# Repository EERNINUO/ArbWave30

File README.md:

<div align="center">

<!-- Assisted-by: DeepSeek - 文档框架 -->

# ArbWave30
30MHz 任意波形发生器 | FPGA + 高速DAC | SCPI 可控 

<p align="center">

  <br/>

  <!--  -->
</p>
</div>

---

> **⚠️ 注意**：你当前查看的是 **develop** 开发分支，内容可能不稳定。
> 推荐使用稳定发布版本：[查看 Releases](https://github.com/EERNINUO/ArbWave30/tree/releases)

## ⚠️ 更新状态
作者正在参与《0854 不相信眼泪》（Author is currently involved in Chinese graduate entrance exam），本项目暂停更新，承诺 2026.12.25 恢复更新并发布第一个 Release。（你问我为什么不是 20 号就更新？好不容易解放了我不得爽玩几天）

## ✨ 特性

### 硬件指标（V1.0）
- 波形：正弦、方波、三角波、噪声波、直流
- 正弦波最高 **30MHz**，方波最高 **5MHz**
- 电压范围（高阻）：20Vpp（DC\~10MHz），14Vpp（10\~20MHz），10Vpp（20\~30MHz）
- 幅值分辨率：2mV（典型），偏移范围 ±10V
- 总谐波失真（THD）：< -50dBc @10MHz 满幅（目标值）
- 相位噪声：-100dBc/Hz @10kHz offset（30MHz 载波）（目标值，受限于测试条件，目前无法标定）
- 输出阻抗：50Ω
- 参考时钟：内部 TCXO（±1ppm）或外部 10MHz 输入

### 硬件指标（MVP）
- 波形：正弦、方波、三角波、噪声波、直流
- 正弦波最高 **30MHz**，方波最高 **5MHz**
- 电压范围（高阻）：4Vpp（DC\~10MHz），2.8Vpp（10\~20MHz），2Vpp（20\~30MHz）
- 幅值分辨率：2mV（典型），偏移范围 ±2V
- 总谐波失真（THD）：< -50dBc @10MHz 满幅（目标值）
- 相位噪声：-80dBc/Hz @10kHz offset（30MHz 载波）（目标值，受限于测试条件，目前无法标定）
- 输出阻抗：50Ω
- 参考时钟：内部 TCXO（±1ppm）

### 控制与接口
- USB 2.0（USB CDC 类），支持 SCPI-1999 命令集
- SMA 输出，SMA 触发 I/O，SMA 外部时钟输入
- 电源输入：24V DC，功耗 <24W

### 软件与扩展路线
- V1.0：单通道 + 基础波形 + 核心 SCPI
- V2.0：双通道 + 调制 + 扫频
- V3.0：Linux GUI + 任意波（16kpts）

---

## 🚦 项目状态

> **当前阶段：MVP 硬件、MCU/FPGA 核心程序验证完成，已能通过 SCPI 控制输出，正在进行模拟前端进一步调优**

### ✅ 已完成
- [x] PCB 设计与打样（4层板，信号完整性设计）
- [x] 模拟前端调试通过 
- [x] DAC 上电参数配置正常（SPI 接口通信稳定）
- [x] 正弦 DDS 核（IP 核实现，48位相位累加器）
- [x] 方波/直流/三角波/噪声波生成
- [x] 幅度控制模块
- [x] 相位控制模块
- [x] SPI Slave 通信接口与寄存器组
- [x] 模拟板驱动库（MCU 端）
- [x] SCPI 协议栈移植
- [x] 7阶椭圆滤波器焊接调试
- [x] 输出性能粗略标定（THD、SFDR）
- [x] 软件幅度校准

### 🏗️ 开发中
- [ ] 谐波性能优化

### 📋 待办（MVP 之后）
- [ ] 滤波器性能优化（重构滤波器，调整群延时，减少快速边沿的过冲/振铃）
- [ ] 分板思路调整（电源板、模拟板、控制板）
- [ ] 模拟板完整版设计（加入 硬件幅度控制、直流偏置、外部触发、外部时钟输入）
- [ ] 输出性能精确标定（需要专业频谱仪，目前无法进行）
- [ ] MCU firmware 迁移到 gcc 工具链
- [ ] 通过 GitHub Action 自动化检查错误/编译
- [ ] 上位机控制软件

### 📸 当前进展

**正弦波输出（SDS824X HD 示波器实测）：**

**正弦波满幅输出波形：**

**方波满幅输出波形：**

> 当前版本方波有约 13.5% 的过冲，为滤波器群延时特性所致，后续将通过优化通道设计解决，详见[重构滤波器调试笔记](docs/设计笔记/重构滤波器调试笔记.md)。

**10MHz正弦波FFT结果：**

经上图数据可计算出[^1]：
  THD ≈ -60.2 dBc @10MHz，
  SFDR[^2] ≈ 63.26 dBc @10MHz

[^1]: 由于示波器自身产生的谐波不可忽略，该值仅供参考，实际值需频谱分析仪复测。

[^2]:SFDR 分为两种定义：1、含谐波；2、不含谐波。由于表中没有非谐波分量，故采用第一种定义。

---

## ⚠️ 已知问题
- 当前版本方波有约 13.5% 的过冲，为滤波器群延时特性所致，后续将通过优化滤波器设计解决。
- 当前版本在运行一段时间后，在输出 25 MHz 以上正弦波时，有概率出现固定大小/方向的偏置抖动，怀疑是 FPGA 发热导致时序漂移，后续将通过优化 FPGA 时序约束和增加散热解决。
- 当前分板设计会导致成品过长过细（约 225mm x 90mm），后续将调整分板方案，分为电源板、模拟板、控制板。

## 🧱 仓库结构
```text
ArbWave30/  
├── docs/ # 设计文档  
│    ├── pic/ # 文档图片  
│    ├── adr/ # 决策记录  
│    ├── 硬件设计文档/ # 硬件设计文档  
│    ├── 设计笔记/ # 设计笔记
│    ├── 用户手册/ # 用户手册  
│    └──  LICENSE # CC BY-SA 4.0  
├── hardware/ # 原理图、PCB源文件   
│    ├── analog_board/ # 模拟板 PCB设计  
│    ├── control_board/ # 控制板 PCB设计  
│    └── LICENSE # CERN-OHL-S-2.0   
├── firmware/ 
│    ├── fpga/ # FPGA 设计源代码（Verilog）  
│    │    ├── Application/ # 项目代码   
│    │    └── FPGA_Test_Hardware/ # FPGA 硬件测试代码   
│    │         ├── FPGA_Clodck_Test/ # 时钟测试代码   
│    │         └── FPGA_Hardware_Test/ # FPGA 硬件测试代码   
│    ├── mcu/ # MCU 固件源代码（C/C++）   
│    │    ├── Application/ # 项目代码   
│    │    ├── MCU_Test_Hardware/ # MCU 硬件测试代码   
│    │    │    └── min_system_test/ # MCU 最小系统测试代码   
│    │    └── SCPI_Test/ # SCPI-parser 移植测试工程   
│    └── Clock_Generator_Config/ # 时钟发生器配置     
├── simulink/ # LTspice 仿真文件  
├── datasheets/ # 组件数据手册，参考设计  
├── scripts/ # 自动化测试脚本（PyVISA）  
│    ├── test_filter/ # 滤波器测试脚本  
│    └── test_diff_to_single # 差分转单端输出测试脚本   
├── LICENSE # GPL-3.0  
└── README.md  
```
---

## 🚀 快速开始

> 项目处于 **最小可行产品（MVP）阶段，未来会出现破坏兼容性的变更**，MVP 已验证通过，Release 打包中，将提供：
> - 打样 PCB 的 Gerber 文件及 BOM
> - FPGA 比特流烧录方法（通过 JTAG 加载）
> - 固件编译与升级步骤

当前你可以浏览 `docs/` 中的设计文档，了解详细的技术规格和设计思路；
或查看 `hardware/` 中的原理图和 PCB 设计文件与 `firmware/` 中的代码框架，了解硬件与软件的构成，并提出您的宝贵意见。

---

## 📡 SCPI 命令示例 

```python
import pyvisa

# 1. 指定纯 Python 后端（无需安装 NI-VISA 驱动）
rm = pyvisa.ResourceManager('@py')

# 2. 列出所有资源，找到你的 COM 口（通常是 'ASRL3::INSTR' 类似格式）
# print(rm.list_resources())

# 3. 打开串口资源，并配置终止符
inst = rm.open_resource('ASRL3::INSTR')  # 请替换为实际的 ASRL 端口号
inst.baud_rate = 115200        # 串口波特率，对于 USB CDC 类设备并不重要
inst.read_termination = '\n'   # 非常重要：库默认是 '\n'，但最好显式声明
inst.write_termination = '\n'  # 发送时自动追加换行符

# 4. 现在你可以像用 USBTMC 仪器一样使用 query
print(inst.query('*IDN?'))
inst.write('SOUR:FREQ 1000')
inst.write('SOUR:STAT ON')

# 5. 查询
freq = inst.query('SOUR:FREQ?')
print(f"Freq: {freq}")

inst.close()
```

完整命令集参见 [docs/SCPI_reference.md](</docs/用户手册/SCPI 参考手册.md>)。

## 🧪 自动化测试
测试脚本位于 `scripts/`（持续更新中），使用 PyVISA 与设备通信。你可以运行对应的脚本进行自动化测试，或者根据你的需求，参考这些脚本自行编写测试用例。

## 📄 文档
设计文档、测试报告和用户手册位于 `docs/`，持续更新中。

## 📅 版本路线图 
| 阶段 | 功能 | 描述 |
|------|------|------|
| V1.0 | 单通道，基础波形（正弦、方波、三角、噪声、DC）| 支持频率、幅值、偏置、相位连续可调；支持SCPI命令（少量核心指令）|
| V2.0 | 双通道 | 增加第二路输出，支持频率/相位同步，相位差可调 |
|      | AM调制 |内/外部调制源，调制深度0\~100% |
| V3.0 | 嵌入式GUI | 基于Linux + LVGL，通过LCD触摸屏直接控制
|      | 任意波 | 支持用户自定义波形表，存储深度≥16kpts |

## 📜 许可证
Copyright © 2026 EERNINUO

本项目采用**多许可证策略**，不同部分适用不同许可证：

| 组成部分 | 许可证 |
|----------|--------|
| 固件 （MCU/FPGA 代码） | [GNU General Public License v3.0](LICENSE) |
| 硬件设计文件 （原理图、PCB、BOM） | [CERN Open Hardware Licence Version 2 - Strongly Reciprocal](hardware/LICENSE) |
| 文档、图片、README | [Creative Commons Attribution-ShareAlike 4.0 International](docs/LICENSE) |

这意味着：
- 你可以自由使用、修改、分享固件代码，但任何衍生代码也必须以 GPL-3.0 开源。
- 你可以基于硬件设计文件制作、分发物理设备，但必须同时开源你对设计文件的修改，并保留署名。
- 你可以复制和修改文档，但必须同样以 CC BY-SA 4.0 分享，并注明原作者。

**商标声明**：`ArbWave30` 名称及标志未经授权不得用于商业产品。

## 🤖 AI 辅助声明

本项目文档框架由 GitHub Copilot / DeepSeek 辅助生成。
作者已逐一审查并测试，但如有任何问题欢迎提交 Issue。

## ⚠️ 免责声明
注意：本项目为个人学习与开源作品，不保证商业级可靠性。使用前请仔细阅读免责声明。

## 📫 联系方式
项目主页: https://github.com/EERNINUO/ArbWave30

## ⭐ Star History
如果您觉得这个项目有帮助，请给一个 Star ⭐，谢谢！

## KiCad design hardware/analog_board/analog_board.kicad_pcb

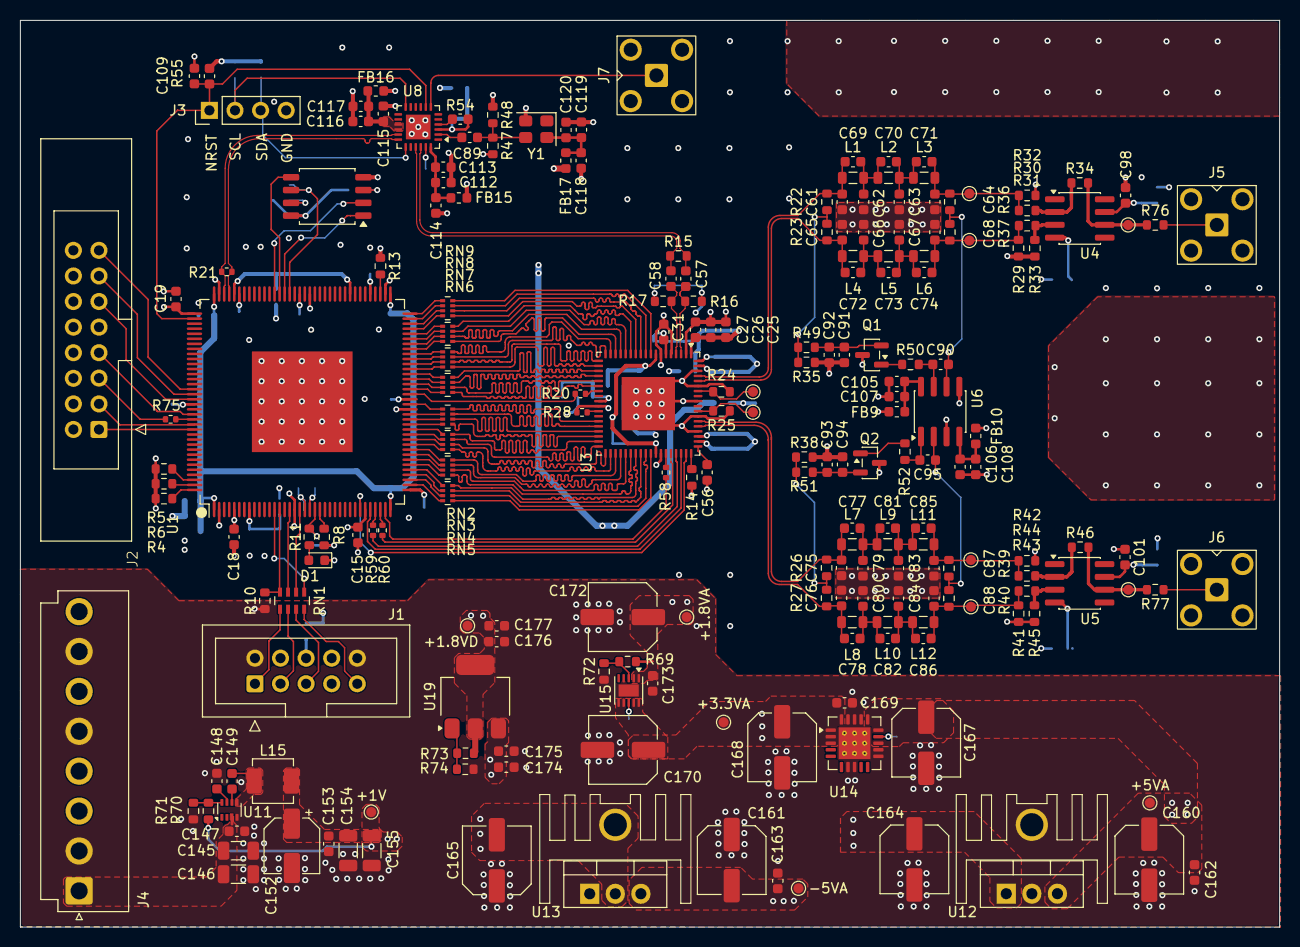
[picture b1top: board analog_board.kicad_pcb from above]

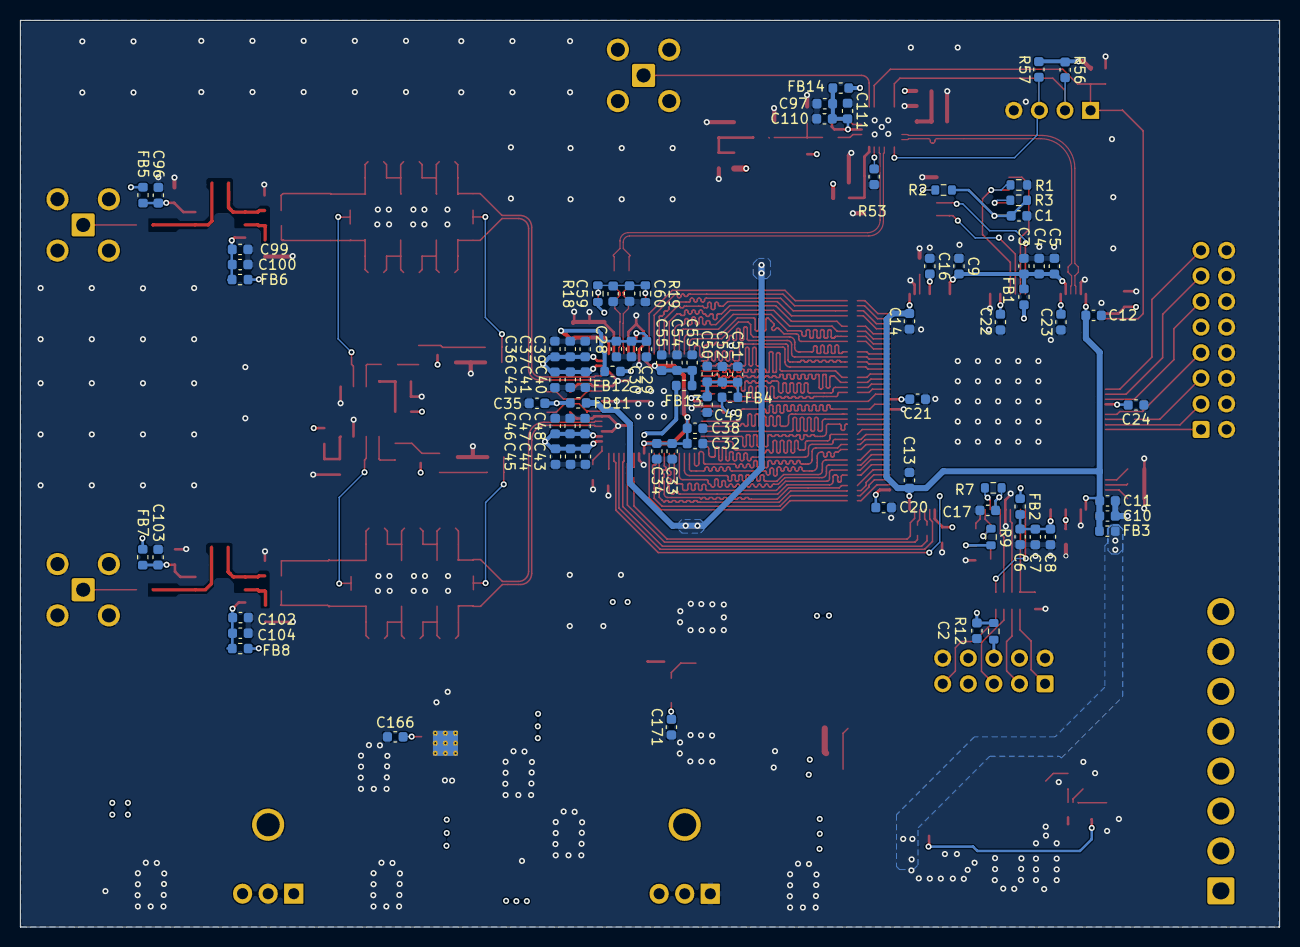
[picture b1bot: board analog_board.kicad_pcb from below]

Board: 4 copper layers, 125.0 x 90.0 mm, 295 parts (84 on the bottom side), 195 nets.

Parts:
C1, C2, C5, C8, C9, C11, C12, C13, C14, C15, C16, C17, C18, C19, C20, C21, C22, C23, C24, C25, C29, C32, C36, C40, C43, C46, C50, C53, C59, C89, C91, C92, C93, C94, C98, C99, C101, C102, C105, C106, C109, C111, C114, C117, C120, C147, C149, C153, C162, C163, C169, C171, C173, C174, C177: 100nF; C_0603_1608Metric
C3, C6, C10, C97, C112, C115, C118: 4.7uF; C_0603_1608Metric
C4, C7: 10nF; C_0603_1608Metric
C26, C30, C33, C37, C41, C44, C47, C51, C54, C60: 1nF; C_0603_1608Metric
C27, C31, C34, C39, C42, C45, C48, C52, C55, C62, C63, C66, C67, C79, C80, C83, C84: 100pF; C_0603_1608Metric
C28, C35, C38, C49, C56, C96, C100, C103, C104, C107, C108, C175, C176: 10uF; C_0603_1608Metric
C57, C58, C166: 1uF; C_0603_1608Metric
C61, C65, C75, C76: 56pF; C_0603_1608Metric
C64, C68, C87, C88: 62pF; C_0603_1608Metric
C69, C72, C77, C78: 6.8p; C_0603_1608Metric
C70, C73, C81, C82: 9.1p; C_0603_1608Metric
C71, C74, C85, C86: 2.0p; C_0603_1608Metric
C90, C95: 100n; C_0603_1608Metric
C110, C113, C116, C119: 470nF; C_0603_1608Metric
C145, C146: 1uF; C_1206_3216Metric
C148: 33nF; C_0603_1608Metric
C152: 22uF; CP_Elec_5x5.4
C154, C155: 22uF; C_1206_3216Metric
C160, C161, C164, C165, C167, C168, C170, C172: 100uF; C_Elec_6.3x7.7
D1: GREEN; LED_0603_1608Metric
FB1: 120R@100MHz; L_0603_1608Metric
FB2, FB3, FB4, FB5, FB6, FB7, FB8, FB9, FB10, FB11, FB12, FB13, FB14, FB15, FB16, FB17: 600R@100MHz; L_0603_1608Metric
HS2, HS4: Heatsink_Pad; TO-220_Heatsink
J1: 2x5 牛角座; IDC-Header_2x05_P2.54mm_Vertical_antiClockWise
J2: Conn_02x08_Counter_Clockwise; IDC_IDC-Header_2x08_P2.54mm_Vertical_antiClockWise
J3: Conn_01x04_Pin; PinHeader_1x04_P2.54mm_Vertical
J4: Conn_01x08; JST_VH_B8P-VH_1x08_P3.96mm_Vertical
J5, J6, J7: CH1; SMA_BAT_Wireless_BWSMA-KWE-Z001
L1, L4, L7, L8: 160n; L_0805_2012Metric
L2, L3, L5, L6, L9, L10, L11, L12: 180n; L_0805_2012Metric
L15: 2.2uH; L_Changjiang_FXL0420
Q1, Q2: MMBT3906; SOT-23
R1, R4, R5, R6: 1kR; R_0603_1608Metric
R2, R3, R7, R8, R9, R10: 4.7kR; R_0603_1608Metric
R11, R35, R38: 0R; R_0603_1608Metric
R12: 33R; R_0603_1608Metric
R13, R14, R36, R37, R39, R40, R71: 10kR; R_0603_1608Metric
R15, R47, R48, R50, R52: 100R; R_0603_1608Metric
R16, R17, R22, R23, R26, R27, R76, R77: 49.9R; R_0603_1608Metric
R18: 1.8kR; R_0603_1608Metric
R19: 510R; R_0603_1608Metric
R20: 0R; R_0402_1005Metric
R21: 100R; R_0402_1005Metric
R24, R25: 499R; R_0603_1608Metric
R28: 4.7k; R_0402_1005Metric
R29, R41: 53.6R; R_0603_1608Metric
R30, R42: 226R; R_0603_1608Metric
R31, R32, R43, R44: 73.2R; R_0603_1608Metric
R33, R34, R45, R46: 442R; R_0603_1608Metric
R49, R51: 68R; R_0603_1608Metric
R53: 10kR; C_0603_1608Metric
R54, R55, R56, R57: 4.7kR; C_0603_1608Metric
R58, R59, R60, R75: 22R; R_0402_1005Metric
R69: 15k; R_0603_1608Metric
R70: 2.4kR; R_0603_1608Metric
R72: 12kR; R_0603_1608Metric
R73: 68kR; R_0603_1608Metric
R74: 7.5kR; R_0603_1608Metric
RN1: 33R; R_Array_Concave_4x0603
RN2, RN3, RN4, RN5, RN6, RN7, RN8, RN9: 33R; R_Array_Concave_4x0402
TP1: CH1_O; TestPoint_Pad_D1.0mm
TP2: CH2_O; TestPoint_Pad_D1.0mm
TP3: CH2_F+; TestPoint_Pad_D1.0mm
TP4: CH2_F-; TestPoint_Pad_D1.0mm
TP5: CH1_F+; TestPoint_Pad_D1.0mm
TP6: CH1_F-; TestPoint_Pad_D1.0mm
TP7: offset1; TestPoint_Pad_D1.0mm
TP8: offset2; TestPoint_Pad_D1.0mm
TP11: +1V; TestPoint_Pad_D1.0mm
TP14: -5VA; TestPoint_Pad_D1.0mm
TP15: +5VA; TestPoint_Pad_D1.0mm
TP16: +3.3VA; TestPoint_Pad_D1.0mm
TP17: +1.8VA; TestPoint_Pad_D1.0mm
TP18: +1.8VD; TestPoint_Pad_D1.0mm
U1: GW2A-LV18EQ144; LQFP-144_20x20_Pitch0.5mm
U2: GD25Q32JVSS; SOIC-8_5.3x5.3mm_P1.27mm
U3: AD9747BCPZ; LFCSP-72-1EP_10x10mm_P0.5mm_EP5.3x5.3mm
U4, U5: OPA695ID; SOIC-8_3.9x4.9mm_P1.27mm
U6: NE5532; SOIC-8_3.9x4.9mm_P1.27mm
U8: CDCI6214RGER; VQFN-24-1EP_4x4mm_P0.5mm_EP2.45x2.45mm
U11: TPS62933; SOT-583-8
U12: L7805; TO-220-3_Vertical
U13: L7905; TO-220-3_Vertical
U14: TPS7A4701xRGW; Texas_RGW0020A_VQFN-20-1EP_5x5mm_P0.65mm_EP3.15x3.15mm_Ther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
U15: TPS7A91; Texas_S-PDSO-N10_EP1.2x2mm
U19: AMS1117; SOT-223-3_TabPin2
Y1: ASE-10MHz; Oscillator_SMD_Abracon_ASE-4Pin_3.2x2.5mm

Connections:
+1.8VA: C172.1, C173.2, FB12.1, R18.2, R69.2, TP17.1 (1_1), U15.1 (OUT), U15.2 (OUT)
+1.8VA_DAC: C25.2, C26.2, C27.2, C28.2, C29.2, C30.2, C31.2, FB12.2, U3.1 (CVDD18), U3.6 (CVDD18)
+1.8VD: C176.2, C177.2, FB13.1, R73.2, TP18.1 (1_1), U19.2 (VO)
+1.8VD_DAC: C32.2, C33.2, C34.2, C38.2, C53.2, C54.2, C55.2, FB13.2, U3.8 (DVDD18), U3.47 (DVDD18)
+1V0: C152.1, C153.2, C154.2, C155.2, FB1.1, FB2.1, FB3.1, L15.2, R70.2, TP11.1 (1_1)
+3.3V: C1.1, C2.2, C15.2, C16.2, C17.2, C18.2, C19.2, C20.2, C21.2, C22.2, C23.2, C24.2, C174.2, C175.2, FB4.1, J4.8, R2.1, R3.1, R7.2, R8.2, R9.2, R12.2, U1.5 (VCCX/VCC_IO2/VCC_IO6/VCC_IO7), U1.19 (VCCX/VCC_IO2/VCC_IO6/VCC_IO7), U1.31 (VCCX/VCC_IO2/VCC_IO6/VCC_IO7), U1.37 (VCC_IO5), U1.55 (VCC_IO4), U1.77 (VCC_IO3), U1.91 (VCC_IO3), U1.103 (VCCX/VCC_IO2/VCC_IO6/VCC_IO7), U1.109 (VCC_IO1), U1.127 (VCC_IO0), U2.8 (VCC), U19.3 (VI)
+3.3VA: C168.1, C169.2, C170.1, FB11.1, FB14.1, FB15.1, FB16.1, FB17.1, TP16.1 (1_1), U14.1 (OUT), U14.2 (NC), U14.3 (SENSE/FB), U14.20 (OUT), U15.6 (SS_CTRL), U15.7 (EN), U15.9 (IN), U15.10 (IN)
+3.3VA_DAC: C35.2, C36.2, C37.2, C39.2, C40.2, C41.2, C42.2, C43.2, C44.2, C45.2, C46.2, C47.2, C48.2, FB11.2, U3.56 (AVDD33), U3.57 (AVDD33), U3.71 (AVDD33), U3.72 (AVDD33)
+3.3VD_DAC: C49.2, C50.2, C51.2, C52.2, FB4.2, U3.27 (DVDD33)
+5VA: C160.1, C162.2, C167.1, FB5.1, FB7.1, FB9.1, TP15.1 (1_1), U12.3 (OUT), U14.13 (EN), U14.15 (IN), U14.16 (IN)
+7V: C164.1, J4.4, U12.1 (IN)
+17V: C145.2, C146.2, C147.2, J4.1, U11.3 (VIN)
-5VA: C161.2, C163.1, FB6.1, FB8.1, FB10.1, Q1.3 (C), Q2.3 (C), TP14.1 (1_1), U13.3 (VO)
-7V: C165.2, HS4.1, J4.6, U13.2 (VI)
/Clock/10MHz_OUT: J7.1 (In), U8.7 (OUT0)
/Clock/CLK_{IN}: C89.2, R47.1, R48.2, Y1.3 (OUT)
/Clock/DAC_CLK+: C57.2, R15.2, U8.22 (OUT1_P)
/Clock/DAC_CLK-: C58.2, R15.1, U8.21 (OUT1_N)
/Clock/FPGA_CLK+: R21.1, U1.105 (IOR7B/RPLL1_C_in), U8.18 (OUT2_P)
/Clock/FPGA_CLK-: R21.2, U1.106 (IOR7A/RPLL1_T_in), U8.17 (OUT2_N)
/Clock/RESET_N: C109.1, J3.1, R55.1, U1.110 (IOT50B), U8.8 (RESETN/SYNC)
/Clock/SCL: J3.2, R56.2, U8.12 (SCL/GPIO3)
/Clock/SDA: J3.3, R57.2, U8.19 (SDA/GPIO2)
/Clock/XIN: C89.1, U8.2 (XIN/FB_N)
/DAC/CLK+: C57.1, R16.2, U3.3 (CLKP)
/DAC/CLK-: C58.1, R17.1, U3.4 (CLKN)
/DAC/DAC_SPI.DAC_RESET: U1.30 (IOL36B), U3.53 (RESET)
/DAC/DAC_SPI.DAC_SPI_CLK: R59.1, U3.51 (SCLK)
/DAC/DAC_SPI.DAC_SPI_CS: U1.32 (IOL42A), U3.52 (CSB)
/DAC/DAC_SPI.DAC_SPI_MISO: R58.1, U1.35 (IOL45B/LPLL2_C_in)
/DAC/DAC_SPI.DAC_SPI_MOSI: R60.1, U3.50 (SDIO)
/DAC/DCO: R20.2, U1.56 (IOB30A/GCLKT_4)
/DAC/FSADJ: R14.2, U3.54 (FSADJ)
/DAC/IOUT1_N: C65.1, C72.2, L4.1, R23.1, U3.68 (IOUT1N)
/DAC/IOUT1_P: C61.2, C69.2, L1.1, R22.2, U3.69 (IOUT1P)
/DAC/IOUT2_N: C75.2, C77.2, L7.1, R26.2, U3.60 (IOUT2N)
/DAC/IOUT2_P: C76.1, C78.2, L8.1, R27.1, U3.59 (IOUT2P)
/DAC/OUT1: R34.2, R76.1, TP1.1 (1_1), U4.6
/DAC/OUT2: R46.2, R77.2, TP2.1 (1_1), U5.6
/DAC/P1D0: RN6.1 (R1.1), U3.24 (P1D0)
/DAC/P1D1: RN6.2 (R2.1), U3.23 (P1D1)
/DAC/P1D2: RN6.3 (R3.1), U3.22 (P1D2)
/DAC/P1D3: RN6.4 (R4.1), U3.21 (P1D3)
/DAC/P1D4: RN7.1 (R1.1), U3.20 (P1D4)
/DAC/P1D5: RN7.2 (R2.1), U3.19 (P1D5)
/DAC/P1D6: RN7.3 (R3.1), U3.18 (P1D6)
/DAC/P1D7: RN7.4 (R4.1), U3.17 (P1D7)
/DAC/P1D8: RN8.1 (R1.1), U3.16 (P1D8)
/DAC/P1D9: RN8.2 (R2.1), U3.15 (P1D9)
/DAC/P1D10: RN8.3 (R3.1), U3.14 (P1D10)
/DAC/P1D11: RN8.4 (R4.1), U3.13 (P1D11)
/DAC/P1D12: RN9.1 (R1.1), U3.12 (P1D12)
/DAC/P1D13: RN9.2 (R2.1), U3.11 (P1D13)
/DAC/P1D14: RN9.3 (R3.1), U3.10 (P1D14)
/DAC/P1D15: RN9.4 (R4.1), U3.9 (P1D15)
/DAC/P2D0: RN5.1 (R1.1), U3.46 (P2D0)
/DAC/P2D1: RN5.2 (R2.1), U3.45 (P2D1)
/DAC/P2D2: RN5.3 (R3.1), U3.44 (P2D2)
/DAC/P2D3: RN5.4 (R4.1), U3.43 (P2D3)
/DAC/P2D4: RN4.1 (R1.1), U3.42 (P2D4)
/DAC/P2D5: RN4.2 (R2.1), U3.41 (P2D5)
/DAC/P2D6: RN4.3 (R3.1), U3.40 (P2D6)
/DAC/P2D7: RN4.4 (R4.1), U3.39 (P2D7)
/DAC/P2D8: RN3.1 (R1.1), U3.38 (P2D8)
/DAC/P2D9: RN3.2 (R2.1), U3.37 (P2D9)
/DAC/P2D10: RN3.3 (R3.1), U3.36 (P2D10)
/DAC/P2D11: RN3.4 (R4.1), U3.35 (P2D11)
/DAC/P2D12: RN2.1 (R1.1), U3.34 (P2D12)
/DAC/P2D13: RN2.2 (R2.1), U3.33 (P2D13)
/DAC/P2D14: RN2.3 (R3.1), U3.32 (P2D14)
/DAC/P2D15: RN2.4 (R4.1), U3.31 (P2D15)
/DAC/REFIO: C56.2, U3.55 (REFIO)
/DAC/offset1: R24.2, TP7.1 (1_1), U3.66 (AUC1P)
/DAC/offset2: R25.2, TP8.1 (1_1), U3.62 (AUX2P)
/FPGA_Config/JTAG_TCK: R10.2, RN1.8 (R1.2), U1.14 (TCK)
/FPGA_Config/JTAG_TDI: RN1.7 (R2.2), U1.16 (TDI)
/FPGA_Config/JTAG_TDO: RN1.6 (R3.2), U1.18 (TDO)
/FPGA_Config/JTAG_TMS: RN1.5 (R4.2), U1.13 (TMS)
/FPGA_Config/MSPI_MCLK: R1.2, U1.93 (MCLK), U2.6 (CLK)
/FPGA_Config/MSPI_MCS: U1.94 (MCS), U2.1 (~CS)
/FPGA_Config/MSPI_MI: U1.96 (MI), U2.2 (DO/IO_{1})
/FPGA_Config/MSPI_MO: U1.95 (MO), U2.5 (DI/IO_{0})
/FPGA_Ctrl.Ctrl_FPGA_NRST: J2.6, U1.126 (IOT23A)
/FPGA_Ctrl.Ctrl_SPI_CLK: J2.2, U1.131 (IOT14B)
/FPGA_Ctrl.Ctrl_SPI_CS: J2.1, U1.132 (IOT14A)
/FPGA_Ctrl.Ctrl_SPI_MISO: J2.3, R75.1
/FPGA_Ctrl.Ctrl_SPI_MOSI: J2.4, U1.129 (IOT17B)
/FPGA_Ctrl.GPIO1: J2.7, U1.125 (IOT22A)
/FPGA_Ctrl.GPIO2: J2.8, U1.124 (IOT23B)
/Power/FB_1.0V: R70.1, R71.2, U11.8 (FB)
Clock_V_{DDIO}: C115.2, C116.2, C117.2, FB16.2, U8.15 (VDDO_34), U8.16 (VDDO_12)
Clock_V_{DD}: C97.2, C110.2, C111.2, FB14.2, R47.2, R54.2, R55.2, R56.1, R57.1, U8.3 (VDD_REF)
Clock_V_{TCXO}: C118.2, C119.2, C120.2, FB17.2, Y1.4 (Vdd)
Clock_V_{VCO}: C112.2, C113.2, C114.2, FB15.2, U8.24 (VDD_VCO)
GND: C1.2, C2.1, C3.1, C4.1, C5.1, C6.1, C7.1, C8.1, C9.1, C10.1, C11.1, C12.1, C13.1, C14.1, C15.1, C16.1, C17.1, C18.1, C19.1, C20.1, C21.1, C22.1, C23.1, C24.1, C25.1, C26.1, C27.1, C28.1, C29.1, C30.1, C31.1, C32.1, C33.1, C34.1, C35.1, C36.1, C37.1, C38.1, C39.1, C40.1, C41.1, C42.1, C43.1, C44.1, C45.1, C46.1, C47.1, C48.1, C49.1, C50.1, C51.1, C52.1, C53.1, C54.1, C55.1, C56.1, C59.1, C60.1, C61.1, C62.1, C63.1, C64.1, C65.2, C66.2, C67.2, C68.2, C75.1, C76.2, C79.1, C80.2, C83.1, C84.2, C87.1, C88.2, C91.1, C92.1, C93.1, C94.1, C96.1, C97.1, C98.1, C99.1, C100.1, C101.1, C102.1, C103.1, C104.1, C105.1, C106.1, C107.1, C108.1, C109.2, C110.1, C111.1, C112.1, C113.1, C114.1, C115.1, C116.1, C117.1, C118.1, C119.1, C120.1, C145.1, C146.1, C147.1, C148.2, C152.2, C153.1, C154.1, C155.1, C160.2, C161.1, C162.1, C163.2, C164.2, C165.1, C166.1, C167.2, C168.2, C169.1, C170.2, C171.1, C172.2, C173.1, C174.1, C175.1, C176.1, C177.1, D1.1 (K), HS2.1, J1.6, J1.10, J2.9, J2.10, J2.11, J2.12, J2.13, J2.14, J2.15, J2.16, J3.4, J4.2, J4.5, J4.7, J5.2 (Ext), J6.2 (Ext), J7.2 (Ext), R1.1, R4.2, R5.2, R6.2, R10.1, R13.1, R14.1, R19.1, R24.1, R25.1, R28.2, R29.2, R30.1, R33.2, R35.1, R38.1, R41.2, R42.1, R45.2, R48.1, R53.1, R71.1, R72.1, R74.1, U1.2 (VSS), U1.17 (VSS), U1.53 (VSS), U1.74 (VSS), U1.89 (VSS), U1.107 (VSS), U1.145 (EPAD), U2.4 (GND), U3.2 (CVSS), U3.5 (CVSS), U3.7 (DVSS), U3.28 (DVSS), U3.48 (DVSS), U3.58 (AVSS), U3.61 (AVSS), U3.64 (AVSS), U3.67 (AVSS), U3.70 (AVSS), U3.73 (EP), U6.3 (+), U6.5 (+), U8.25 (GND), U11.4 (GND), U12.2 (GND), U13.1 (GND), U14.7 (GND), U14.8 (1.6V), U14.11 (0.2V), U14.12 (0.1V), U14.17 (NC), U14.18 (NC), U14.19 (NC), U14.21 (EP), U15.4 (GND), U15.11 (GND), Y1.2 (GND)
unnamed: C59.2, C60.2, R16.1, R17.2, R18.1, R19.2
unnamed: C62.2, C69.1, C70.2, L1.2, L2.1
unnamed: C63.2, C70.1, C71.2, L2.2, L3.1
unnamed: C64.2, C71.1, L3.2, R30.2, R32.1, R36.2, TP6.1 (1_1)
unnamed: C66.1, C72.1, C73.2, L4.2, L5.1
unnamed: C67.1, C73.1, C74.2, L5.2, L6.1
unnamed: C68.1, C74.1, L6.2, R29.1, R31.1, R37.1, TP5.1 (1_1)
unnamed: C77.1, C79.2, C81.2, L7.2, L9.1
unnamed: C78.1, C80.1, C82.2, L8.2, L10.1
unnamed: C81.1, C83.2, C85.2, L9.2, L11.1
unnamed: C82.1, C84.1, C86.2, L10.2, L12.1
unnamed: C85.1, C87.2, L11.2, R39.2, R42.2, R44.1, TP3.1 (1_1)
unnamed: C86.1, C88.1, L12.2, R40.1, R41.1, R43.1, TP4.1 (1_1)
unnamed: C90.2, R50.1, U6.7
unnamed: C95.2, R52.1, U6.1
unnamed: D1.2 (A), R11.2
unnamed: J1.1, RN1.1 (R1.1)
unnamed: J1.2, RN1.2 (R2.1)
unnamed: J1.3, RN1.3 (R3.1)
unnamed: J1.5, RN1.4 (R4.1)
unnamed: J1.8, R12.1
unnamed: J5.1 (In), R76.2
unnamed: J6.1 (In), R77.1
unnamed: Q1.1 (B), R50.2
unnamed: C91.2, C92.2, Q1.2 (E), R49.2
unnamed: Q2.1 (B), R52.2
unnamed: C93.2, C94.2, Q2.2 (E), R51.2
unnamed: R22.1, R23.2, R35.2, R49.1
unnamed: R26.1, R27.2, R38.2, R51.1
unnamed: RN2.8 (R1.2), U1.50 (IOB20A)
unnamed: RN2.7 (R2.2), U1.51 (IOB20B)
unnamed: RN2.6 (R3.2), U1.52 (IOB22A)
unnamed: RN2.5 (R4.2), U1.54 (IOB22B)
unnamed: RN3.8 (R1.2), U1.46 (IOB14A)
unnamed: RN3.7 (R2.2), U1.47 (IOB14B)
unnamed: RN3.6 (R3.2), U1.48 (IOB17A)
unnamed: RN3.5 (R4.2), U1.49 (IOB17B)
unnamed: RN4.8 (R1.2), U1.42 (IOB7A)
unnamed: RN4.7 (R2.2), U1.43 (IOB7B)
unnamed: RN4.6 (R3.2), U1.44 (IOB12A)
unnamed: RN4.5 (R4.2), U1.45 (IOB12B)
unnamed: RN5.8 (R1.2), U1.38 (IOB5A)
unnamed: RN5.7 (R2.2), U1.39 (IOB5B)
unnamed: RN5.6 (R3.2), U1.40 (IOB6A)
unnamed: RN5.5 (R4.2), U1.41 (IOB6B)
unnamed: RN6.8 (R1.2), U1.57 (IOB30B/GCLKC_4)
unnamed: RN6.7 (R2.2), U1.58 (IOB33A)
unnamed: RN6.6 (R3.2), U1.59 (IOB33B)
unnamed: RN6.5 (R4.2), U1.60 (IOB34A)
unnamed: RN7.8 (R1.2), U1.61 (IOB34B)
unnamed: RN7.7 (R2.2), U1.62 (IOB38A)
unnamed: RN7.6 (R3.2), U1.63 (IOB38B)
unnamed: RN7.5 (R4.2), U1.64 (IOB40A)
unnamed: RN8.8 (R1.2), U1.65 (IOB40B)
unnamed: RN8.7 (R2.2), U1.66 (IOB42A)
unnamed: RN8.6 (R3.2), U1.67 (IOB42B)
unnamed: RN8.5 (R4.2), U1.68 (IOB48A)
unnamed: RN9.8 (R1.2), U1.69 (IOB48B)
unnamed: RN9.7 (R2.2), U1.70 (IOB53A)
unnamed: RN9.6 (R3.2), U1.71 (IOB53B)
unnamed: RN9.5 (R4.2), U1.72 (IOB55B)
unnamed: R9.1, R11.1, U1.21 (DONE)
unnamed: R13.2, U1.75 (EXTR)
unnamed: R4.1, U1.144 (MODE0)
unnamed: R5.1, U1.142 (MODE1)
unnamed: R6.1, U1.143 (MODE2)
unnamed: R8.1, U1.22 (READY)
unnamed: R7.1, U1.20 (RECONFIG_N)
unnamed: R75.2, U1.130 (IOT17A)
unnamed: R59.2, U1.33 (IOL42B)
unnamed: R60.2, U1.34 (IOL45A/LPLL2_T_in)
unnamed: R3.2, U2.7 (~HOLD/~RESET/IO_{3})
unnamed: R2.2, U2.3 (~WP/IO_{2})
unnamed: R20.1, U3.25 (DCO)
unnamed: R28.1, U3.29 (IQSEL)
unnamed: R58.2, U3.49 (SDO)
unnamed: R31.2, R33.1, U4.3 (+)
unnamed: R32.2, R34.1, U4.2 (-)
unnamed: C96.2, C98.2, FB5.2, U4.7 (V+)
unnamed: C99.2, C100.2, FB6.2, U4.4 (V-)
unnamed: R43.2, R45.1, U5.3 (+)
unnamed: R44.2, R46.1, U5.2 (-)
unnamed: C101.2, C103.2, FB7.2, U5.7 (V+)
unnamed: C102.2, C104.2, FB8.2, U5.4 (V-)
unnamed: C95.1, R39.1, R40.2, U6.2 (-)
unnamed: C90.1, R36.1, R37.2, U6.6 (-)
unnamed: C105.2, C107.2, FB9.2, U6.8 (V+)
unnamed: C106.2, C108.2, FB10.2, U6.4 (V-)
unnamed: R53.2, U8.23 (EEPROM_SEL)
unnamed: R54.1, U8.4 (REFSEL)
unnamed: C149.2, U11.6 (BST)
unnamed: C148.1, U11.7 (SS)
unnamed: C149.1, L15.1, U11.5 (SW)
unnamed: C166.2, U14.14 (NR)
unnamed: R69.1, R72.2, U15.3 (FB)
unnamed: C171.2, U15.8 (NR/SS)
unnamed: R73.1, R74.2, U19.1 (ADJ)
VCC_Core: C10.2, C11.2, C12.2, C13.2, C14.2, FB3.2, U1.1 (VCC/VCC_PLLL1), U1.36 (VCC/VCC_PLLL1), U1.73 (VCC/VCC_PLLL1), U1.108 (VCC/VCC_PLLL1)
VCC_PLLL: C6.2, C7.2, C8.2, FB2.2, U1.8 (VCCPLL_L0)
VCC_PLLR: C3.2, C4.2, C5.2, C9.2, FB1.2, U1.81 (VCCPLL_R1), U1.104 (VCCPLL_R0)

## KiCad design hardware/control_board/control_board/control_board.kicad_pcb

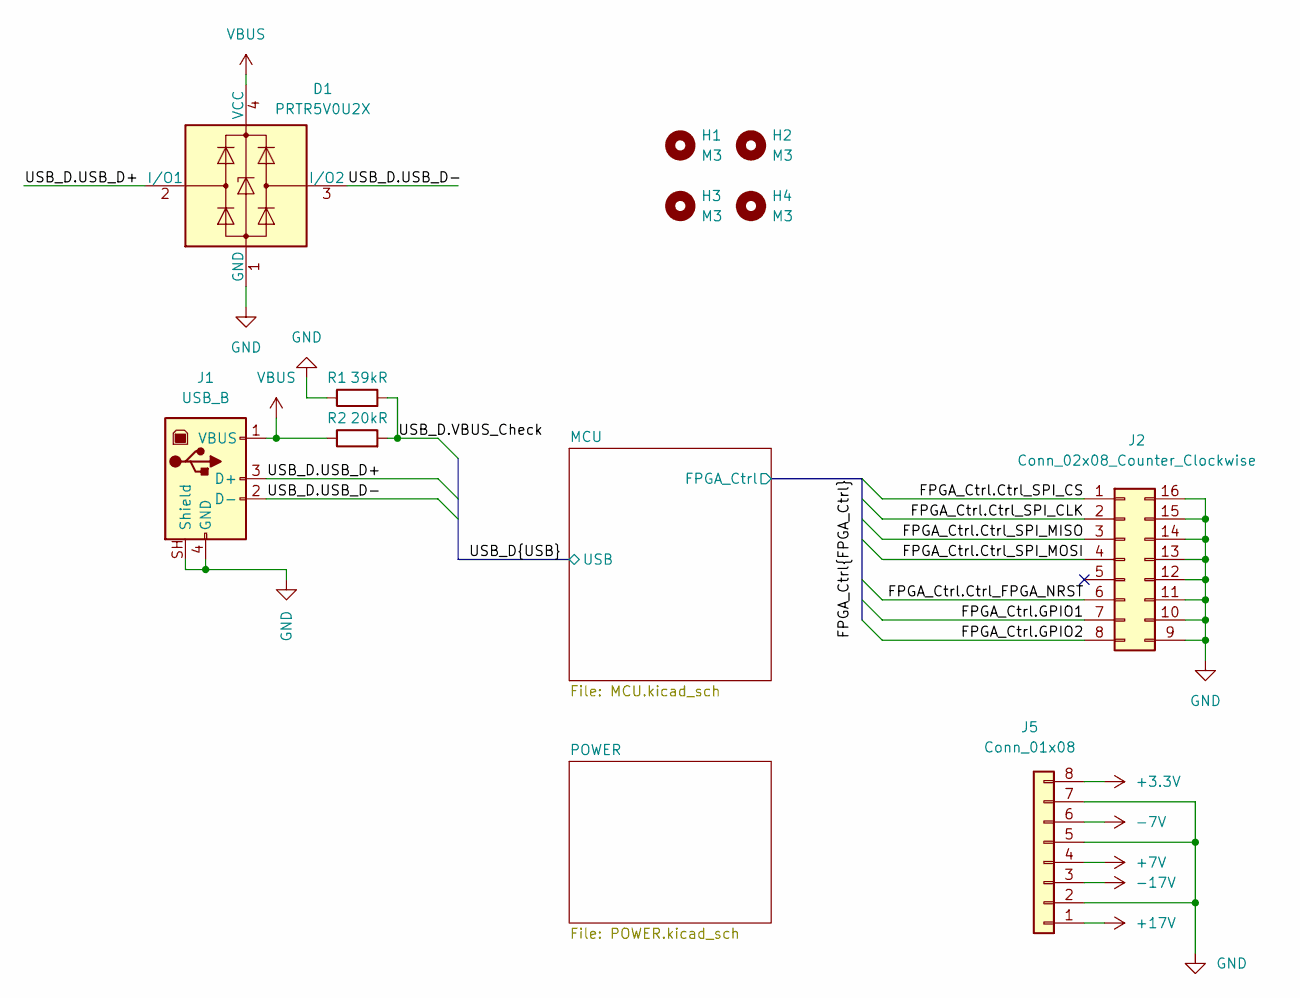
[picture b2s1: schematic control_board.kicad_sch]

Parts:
D1: PRTR5V0U2X; SOT-143
H1, H2, H3, H4: M3; MountingHole_3.2mm_M3
J1: USB_B; USB_B_Lumberg_2411_02_Horizontal
J2: Conn_02x08_Counter_Clockwise; IDC_IDC-Header_2x08_P2.54mm_Vertical_antiClockWise
J5: Conn_01x08; JST_VH_B8P-VH_1x08_P3.96mm_Vertical
R1: 39kR; R_0603_1608Metric
R2: 20kR; R_0603_1608Metric

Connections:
+3.3V: J5.8; also elsewhere on the board
+7V: J5.4; also elsewhere on the board
+17V: J5.1; also elsewhere on the board
-7V: J5.6; also elsewhere on the board
-17V: J5.3; also elsewhere on the board
/FPGA_Ctrl.Ctrl_FPGA_NRST: J2.6; also elsewhere on the board
/FPGA_Ctrl.Ctrl_SPI_CLK: J2.2; also elsewhere on the board
/FPGA_Ctrl.Ctrl_SPI_CS: J2.1; also elsewhere on the board
/FPGA_Ctrl.Ctrl_SPI_MISO: J2.3; also elsewhere on the board
/FPGA_Ctrl.Ctrl_SPI_MOSI: J2.4; also elsewhere on the board
/FPGA_Ctrl.GPIO1: J2.7; also elsewhere on the board
/FPGA_Ctrl.GPIO2: J2.8; also elsewhere on the board
/USB_D.USB_D+: D1.2 (I/O1), J1.3 (D+); also elsewhere on the board
/USB_D.USB_D-: D1.3 (I/O2), J1.2 (D-); also elsewhere on the board
/USB_D.VBUS_Check: R1.2, R2.2; also elsewhere on the board
GND: D1.1 (GND), J1.4 (GND), J1.SH (Shield), J2.9, J2.10, J2.11, J2.12, J2.13, J2.14, J2.15, J2.16, J5.2, J5.5, J5.7, R1.1; also elsewhere on the board
VBUS: D1.4 (VCC), J1.1 (VBUS), R2.1

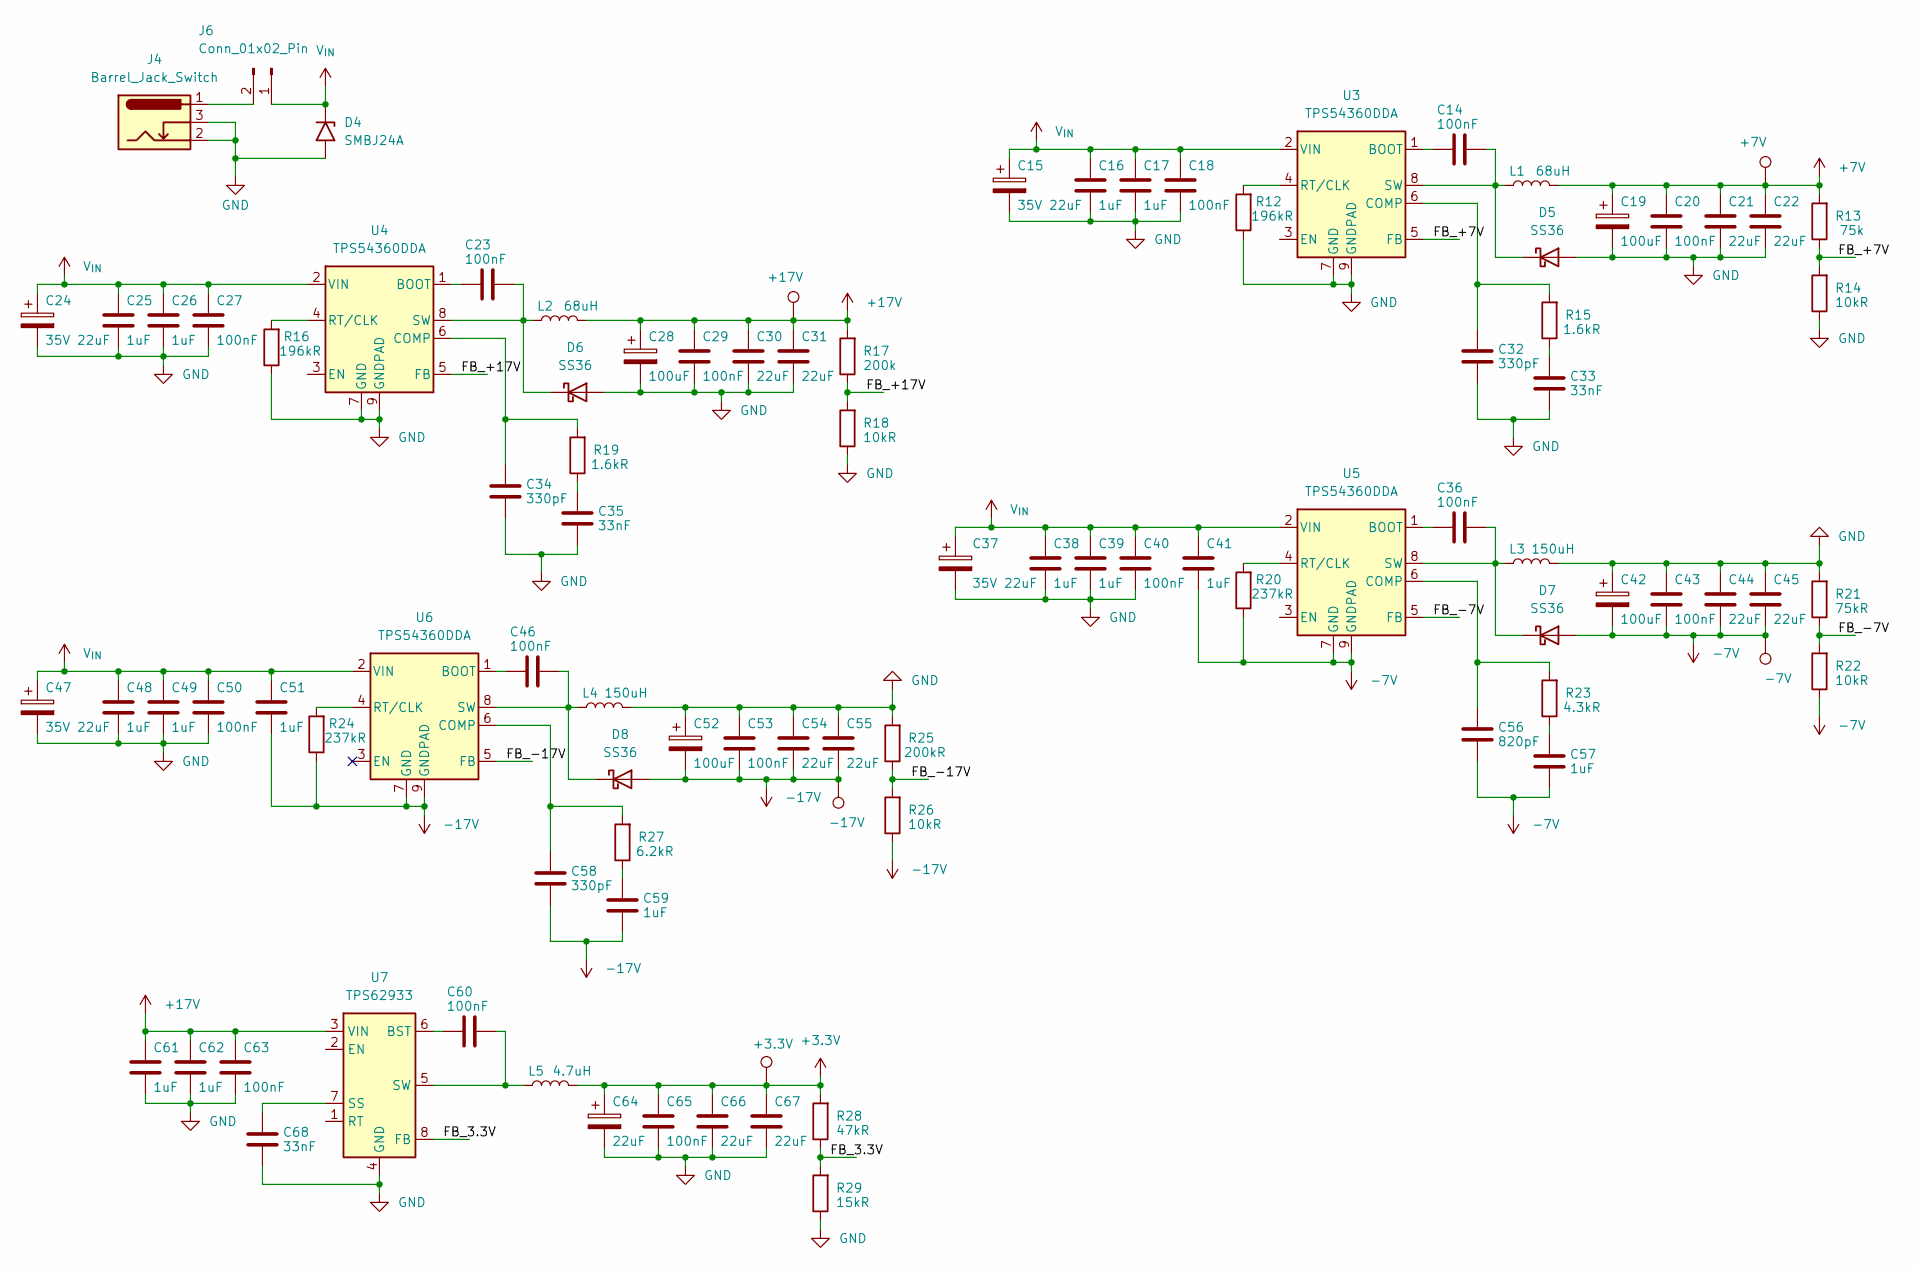
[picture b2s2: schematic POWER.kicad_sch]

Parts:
C14, C18, C20, C23, C27, C29, C36, C40, C43, C46, C50, C53, C60, C63, C65: 100nF; C_0603_1608Metric
C15, C24, C37, C47: 35V 22uF; CP_Elec_5x5.4
C16, C17, C25, C26, C38, C39, C48, C49, C61, C62: 1uF; C_1206_3216Metric
C19, C28, C42, C52: 100uF; C_Elec_6.3x7.7
C21, C22, C30, C31, C44, C45, C54, C55, C66, C67: 22uF; C_1206_3216Metric
C32, C34, C58: 330pF; C_0603_1608Metric
C33, C35, C68: 33nF; C_0603_1608Metric
C41, C51, C57, C59: 1uF; C_0603_1608Metric
C56: 820pF; C_0603_1608Metric
C64: 22uF; CP_Elec_5x5.4
D4: SMBJ24A; D_SMB
D5, D6, D7, D8: SS36; D_SMA
J4: Barrel_Jack_Switch; BarrelJack_GCT_DCJ200-10-A_Horizontal
J6: Conn_01x02_Pin; JST_VH_B2P-VH-B_1x02_P3.96mm_Vertical
L1, L2: 68uH; L_Changjiang_FXL1040
L3, L4: 150uH; L_12x12mm_H6mm
L5: 4.7uH; L_Changjiang_FXL0420
R12, R16: 196kR; R_0603_1608Metric
R13: 75k; R_0603_1608Metric
R14, R18, R22, R26: 10kR; R_0603_1608Metric
R15, R19: 1.6kR; R_0603_1608Metric
R17: 200k; R_0603_1608Metric
R20, R24: 237kR; R_0603_1608Metric
R21: 75kR; R_0603_1608Metric
R23: 4.3kR; R_0603_1608Metric
R25: 200kR; R_0603_1608Metric
R27: 6.2kR; R_0603_1608Metric
R28: 47kR; R_0603_1608Metric
R29: 15kR; R_0603_1608Metric
TP7: +7V; TestPoint_Pad_D1.0mm
TP8: +17V; TestPoint_Pad_D1.0mm
TP9: -7V; TestPoint_Pad_D1.0mm
TP10: -17V; TestPoint_Pad_D1.0mm
TP11: +3.3V; TestPoint_Pad_D1.0mm
U3, U4, U5, U6: TPS54360DDA; TI_SO-PowerPAD-8_ThermalVias
U7: TPS62933; SOT-583-8

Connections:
+3.3V: C64.1, C65.2, C66.2, C67.2, L5.2, R28.2, TP11.1 (1_1); also elsewhere on the board
+7V: C19.1, C20.2, C21.2, C22.2, L1.2, R13.2, TP7.1 (1_1); also elsewhere on the board
+17V: C28.1, C29.2, C30.2, C31.2, C61.2, C62.2, C63.2, L2.2, R17.2, TP8.1 (1_1), U7.3 (VIN); also elsewhere on the board
-7V: C41.1, C42.2, C43.1, C44.1, C45.1, C56.2, C57.2, D7.2 (A), R20.1, R22.1, TP9.1 (1_1), U5.7 (GND), U5.9 (GNDPAD); also elsewhere on the board
-17V: C51.1, C52.2, C53.1, C54.1, C55.1, C58.2, C59.2, D8.2 (A), R24.1, R26.1, TP10.1 (1_1), U6.7 (GND), U6.9 (GNDPAD); also elsewhere on the board
/POWER/FB_3.3V: R28.1, R29.2, U7.8 (FB)
/POWER/FB_+7V: R13.1, R14.2, U3.5 (FB)
/POWER/FB_+17V: R17.1, R18.2, U4.5 (FB)
/POWER/FB_-7V: R21.1, R22.2, U5.5 (FB)
/POWER/FB_-17V: R25.1, R26.2, U6.5 (FB)
GND: C15.2, C16.1, C17.1, C18.1, C19.2, C20.1, C21.1, C22.1, C24.2, C25.1, C26.1, C27.1, C28.2, C29.1, C30.1, C31.1, C32.2, C33.2, C34.2, C35.2, C37.2, C38.1, C39.1, C40.1, C42.1, C43.2, C44.2, C45.2, C47.2, C48.1, C49.1, C50.1, C52.1, C53.2, C54.2, C55.2, C61.1, C62.1, C63.1, C64.2, C65.1, C66.1, C67.1, C68.2, D4.2 (A2), D5.2 (A), D6.2 (A), J4.2, J4.3, L3.2, L4.2, R12.1, R14.1, R16.1, R18.1, R21.2, R25.2, R29.1, U3.7 (GND), U3.9 (GNDPAD), U4.7 (GND), U4.9 (GNDPAD), U7.4 (GND); also elsewhere on the board
unnamed: C33.1, R15.1
unnamed: C35.1, R19.1
unnamed: C57.1, R23.1
unnamed: C59.1, R27.1
unnamed: C14.1, D5.1 (K), L1.1, U3.8 (SW)
unnamed: C23.1, D6.1 (K), L2.1, U4.8 (SW)
unnamed: C36.1, D7.1 (K), L3.1, U5.8 (SW)
unnamed: C46.1, D8.1 (K), L4.1, U6.8 (SW)
unnamed: J4.1, J6.2
unnamed: C14.2, U3.1 (BOOT)
unnamed: C32.1, R15.2, U3.6 (COMP)
unnamed: R12.2, U3.4 (RT/CLK)
unnamed: C23.2, U4.1 (BOOT)
unnamed: C34.1, R19.2, U4.6 (COMP)
unnamed: R16.2, U4.4 (RT/CLK)
unnamed: C36.2, U5.1 (BOOT)
unnamed: C56.1, R23.2, U5.6 (COMP)
unnamed: R20.2, U5.4 (RT/CLK)
unnamed: C46.2, U6.1 (BOOT)
unnamed: C58.1, R27.2, U6.6 (COMP)
unnamed: R24.2, U6.4 (RT/CLK)
unnamed: C60.2, U7.6 (BST)
unnamed: C68.1, U7.7 (SS)
unnamed: C60.1, L5.1, U7.5 (SW)
V_{IN}: C15.1, C16.2, C17.2, C18.2, C24.1, C25.2, C26.2, C27.2, C37.1, C38.2, C39.2, C40.2, C41.2, C47.1, C48.2, C49.2, C50.2, C51.2, D4.1 (A1), J6.1, U3.2 (VIN), U4.2 (VIN), U5.2 (VIN), U6.2 (VIN)
